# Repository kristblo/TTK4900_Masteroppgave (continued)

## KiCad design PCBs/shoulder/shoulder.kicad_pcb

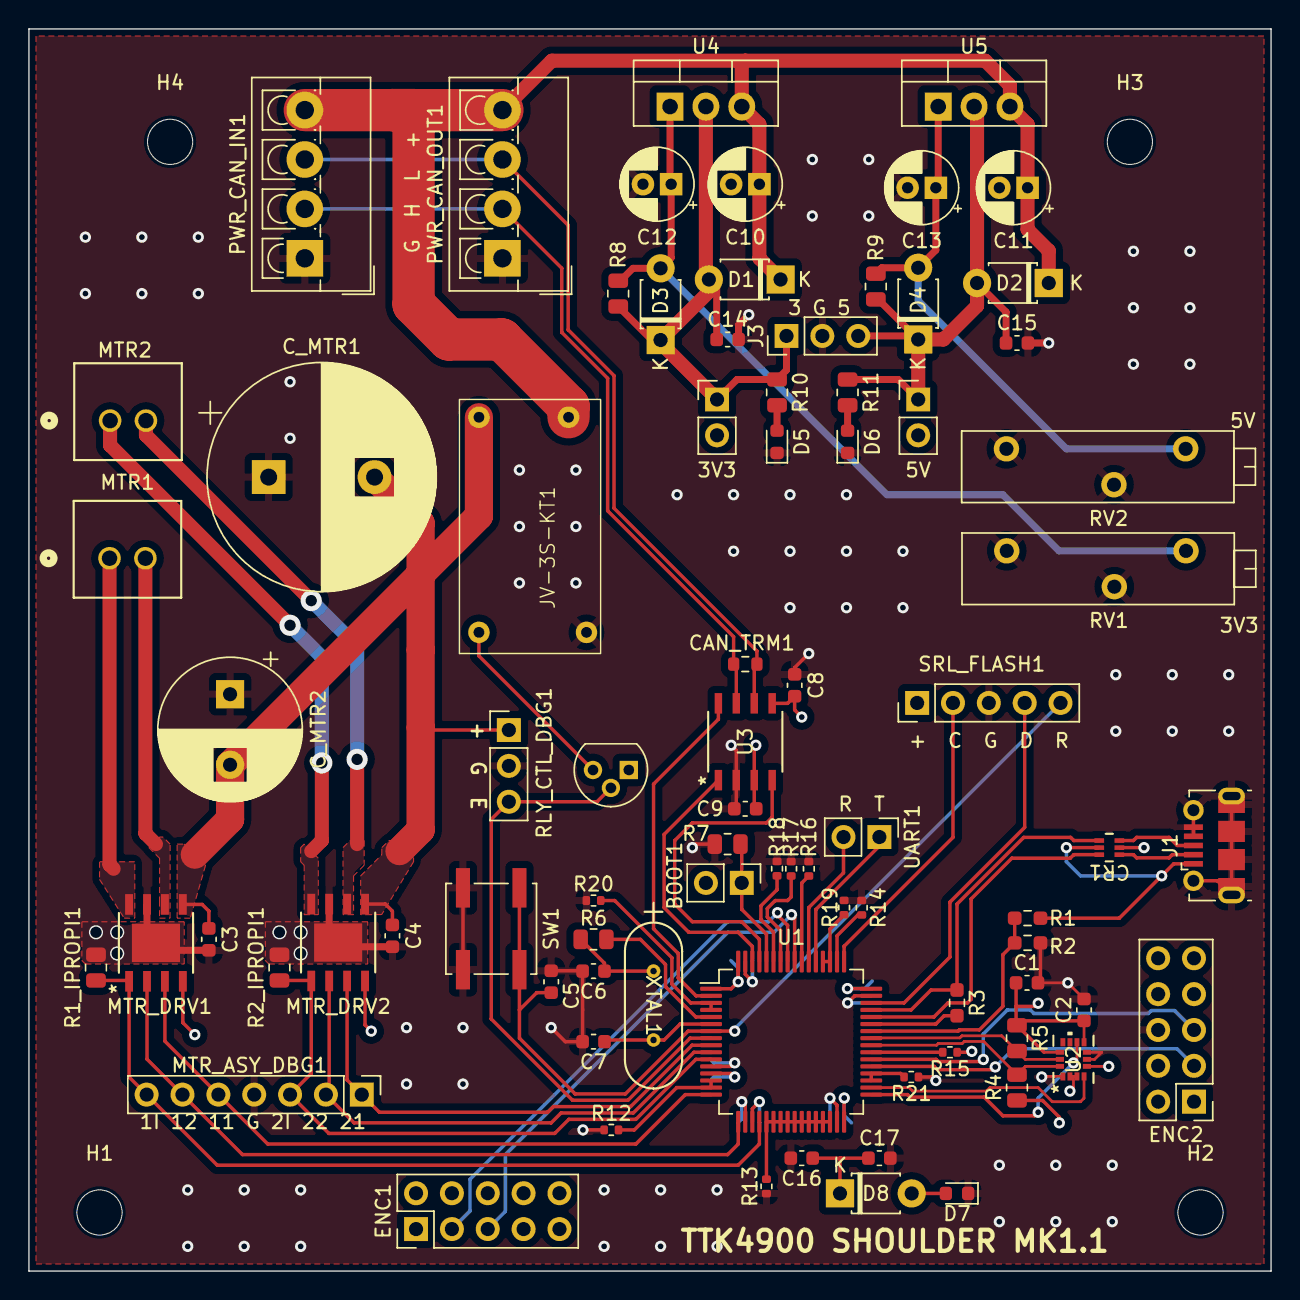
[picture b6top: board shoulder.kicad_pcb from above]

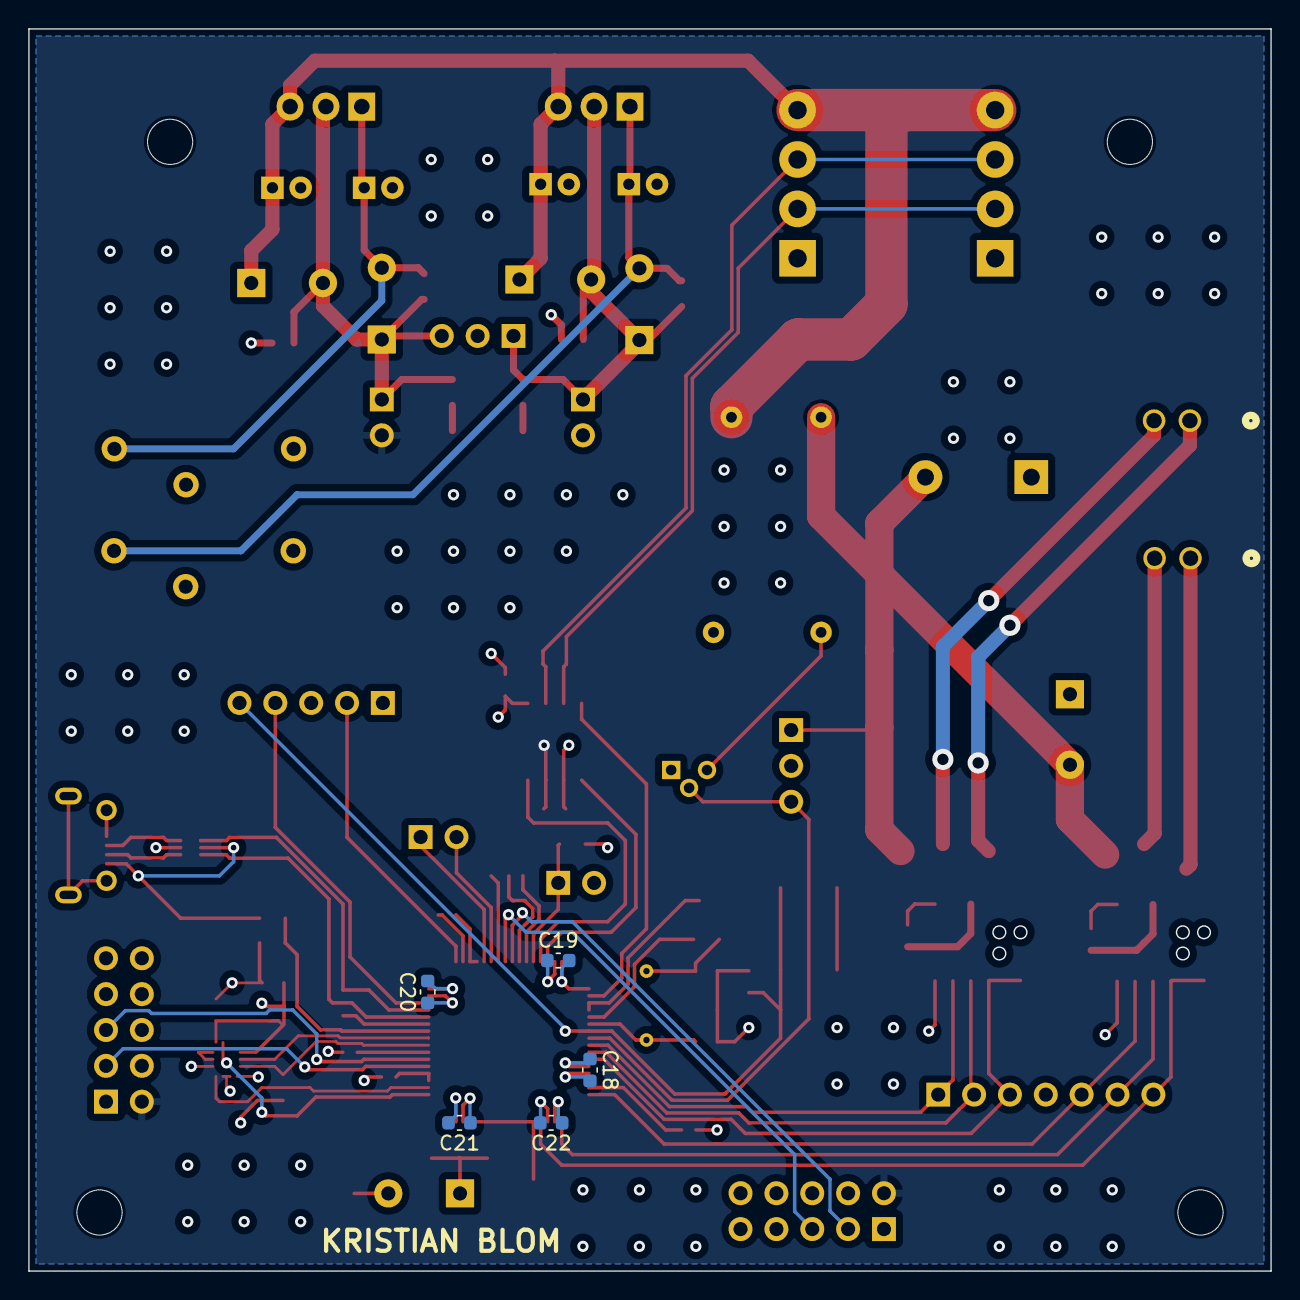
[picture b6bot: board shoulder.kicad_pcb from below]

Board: 4 copper layers, 88.0 x 88.0 mm, 89 parts (5 on the bottom side), 63 nets.

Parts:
BOOT1: BOOTMODE; PinHeader_1x02_P2.54mm_Vertical
C1, C2, C3, C4, C5, C8, C9, C14, C15, C19, C20, C21, C22: 100nF; C_0603_1608Metric
C6, C7: 20pF; C_0603_1608Metric
C10, C11, C12, C13: 10muF; CP_Radial_D5.0mm_P2.00mm
C16: 4.7muF; C_0603_1608Metric
C17: 1muF; C_0603_1608Metric
C18: 10nF; C_0603_1608Metric
CAN_TRM1: 120Ohm; R_0603_1608Metric
CR1: USBLC6-2P6; SOT-666_STM
C_MTR1: 330muF; CP_Radial_D16.0mm_P7.50mm
C_MTR2: 220muF; CP_Radial_D10.0mm_P5.00mm
D1, D2, D3, D4: IN4005; D_T-1_P5.08mm_Horizontal
D5: LED_3V3; LED_0603_1608Metric
D6: LED_5V; LED_0603_1608Metric
D7: LED; LED_0603_1608Metric
D8: D_Zener; D_T-1_P5.08mm_Horizontal
ENC1, ENC2: Conn_02x05_Odd_Even; PinHeader_2x05_P2.54mm_Vertical
H1, H2, H3, H4: MountingHole; MountingHole_3.2mm_M3
J1: USB_B_Micro; USB_Micro-B_Molex-105017-0001
J2: Conn_01x07; PinHeader_1x07_P2.54mm_Vertical
J3: Conn_01x03; PinHeader_1x03_P2.54mm_Vertical
JP1, JP2: Jumper_2_Open; PinHeader_1x02_P2.54mm_Vertical
JV-3S-KT1: RELAY; JV-3S-KT
MTR1, MTR2: 705430001; 70543-0001_MOL
MTR_DRV1, MTR_DRV2: DRV8251ADDAR; SOIC8_DDA_TEX
PWR_CAN_IN1: Conn_01x04; TerminalBlock_4Ucon_1x04_P3.50mm_Vertical
PWR_CAN_OUT1: Conn_01x04; TerminalBlock_4Ucon_1x04_P3.50mm_Vertical
Q1_RLY_CTRL1: Q_NIGBT_CGE; TO-92
R1: 82k; R_0603_1608Metric_Pad0.98x0.95mm_HandSolder
R1_IPROPI1, R2_IPROPI1: 510Ohm; R_0805_2012Metric
R2: 33k; R_0603_1608Metric_Pad0.98x0.95mm_HandSolder
R3: 1k5; R_0603_1608Metric_Pad0.98x0.95mm_HandSolder
R4, R5: 10k; R_0805_2012Metric
R6: 340Ohm; R_0805_2012Metric
R7: 10kOhm; R_0805_2012Metric
R8, R9: 240Ohm; R_0805_2012Metric
R10, R11: 1k5; R_0805_2012Metric
R12, R13, R14, R15, R16, R17, R18, R19, R20, R21: 40kOhm; R_0402_1005Metric
RLY_CTL_DBG1: Conn_01x03; PinHeader_1x03_P2.54mm_Vertical
RV1: 0,386k; Potentiometer_Bourns_3006P_Horizontal
RV2: 0,706k; Potentiometer_Bourns_3006P_Horizontal
SRL_FLASH1: Conn_01x05; PinHeader_1x05_P2.54mm_Vertical
SW1: RESET; SW_Push_1P1T_NO_CK_KSC6xxJ
U1: STM32F303RETx; LQFP-64_10x10mm_P0.5mm
U2: LSM6DSMTR; LGA-14L_2P5X3X0P83_STM
U3: TJA1057GT/3J; SOT96-1_SO8_NXP
U4, U5: LM317_TO-220; TO-220-3_Vertical
UART1: Conn_01x02; PinHeader_1x02_P2.54mm_Vertical
XTAL1: ABL-16.000MHZ-B2; XTAL_ABL-16_ABR

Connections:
+3V3: BOOT1.2 (B), C1.1, C2.1, C8.1, C16.1, C17.1, C18.2, C19.2, C20.2, C21.2, C22.2, D8.1 (K), JP1.2 (B), MTR_DRV1.4 (VREF), MTR_DRV2.4 (VREF), Q1_RLY_CTRL1.1 (C), R4.1, R5.1, SRL_FLASH1.1, U1.1 (VBAT), U1.13 (VDDA), U1.19 (VDD), U1.32 (VDD), U1.48 (VDD), U1.64 (VDD), U2.2 (SDx), U2.3 (SCx), U2.5 (VDDIO), U2.8 (VDD), U2.12 (CS), U3.5 (VIO)
+5V: C9.1, ENC1.2, ENC2.2, JP2.2 (B), U3.3 (VCC)
+48V: C10.1, C11.1, D1.1 (K), D2.1 (K), JV-3S-KT1.3 (NO), PWR_CAN_IN1.4 (48V), PWR_CAN_OUT1.4 (48V), U4.3 (VI), U5.3 (VI)
/BOOT0: BOOT1.1 (A), R7.2, U1.60 (BOOT0)
/CANH: CAN_TRM1.2, PWR_CAN_IN1.2 (CANH), PWR_CAN_OUT1.2 (CANH), U3.7 (CANH)
/CANL: CAN_TRM1.1, PWR_CAN_IN1.3 (CANL), PWR_CAN_OUT1.3 (CANL), U3.6 (CANL)
/CAN_EN: U1.2 (PC13), U3.8 (S)
/CAN_RX: U1.61 (CAN_RX), U3.4 (RXD)
/CAN_TX: U1.62 (CAN_TX), U3.1 (TXD)
/DRV1_IN1: J2.5, MTR_DRV1.3 (IN1), U1.16 (TIM15_CH1)
/DRV1_IN2: J2.6, MTR_DRV1.2 (IN2), U1.17 (TIM15_CH2)
/DRV1_IPROPI: J2.7, MTR_DRV1.1 (IPROPI), R1_IPROPI1.1, U1.20 (ADC2_IN1)
/DRV2_IN1: J2.1, MTR_DRV2.3 (IN1), U1.9 (TIM1_CH2)
/DRV2_IN2: J2.2, MTR_DRV2.2 (IN2), U1.10 (TIM1_CH3)
/DRV2_IPROPI: J2.3, MTR_DRV2.1 (IPROPI), R2_IPROPI1.1, U1.11 (ADC2_IN9)
/ENC1A: ENC1.5, U1.56 (TIM3_CH1)
/ENC1B: ENC1.3, U1.57 (TIM3_CH2)
/ENC2A: ENC2.5, U1.38 (TIM8_CH2)
/ENC2B: ENC2.3, U1.37 (TIM8_CH1)
/FLASH_CLK: SRL_FLASH1.2, U1.49 (SYS_JTCK-SWCLK)
/FLASH_DIO: SRL_FLASH1.4, U1.46 (SYS_JTMS-SWDIO)
/GND_RES1: R13.2, U1.21 (PA5), U1.22 (PA6), U1.23 (PA7), U1.24 (PC4), U1.25 (PC5), U1.26 (PB0), U1.27 (PB1), U1.28 (PB2), U1.29 (PB10), U1.30 (PB11)
/I2C_SCL: R5.2, U1.41 (I2C3_SCL), U2.13 (SCL)
/I2C_SDA: R4.2, U1.40 (I2C3_SDA), U2.14 (SDA)
/IMU_IN2: U1.33 (PB12), U2.9 (INT2)
/IMU_INT1: U1.34 (PB13), U2.4 (INT1)
/OSC_IN: R6.1, U1.5 (RCC_OSC_IN)
/OSC_OUT: C7.1, U1.6 (RCC_OSC_OUT), XTAL1.2
/RELAY_EN: Q1_RLY_CTRL1.2 (G), RLY_CTL_DBG1.3, U1.8 (PC0)
/RESET: C5.2, SRL_FLASH1.5, SW1.3 (K), SW1.4 (A), U1.7 (NRST)
/UART_RX: U1.54 (UART5_RX), UART1.2
/UART_TX: U1.53 (UART5_TX), UART1.1
/USB_DM: CR1.6 (I/O1), U1.44 (USB_DM)
/USB_DP: CR1.4 (I/O2), R3.1, U1.45 (USB_DP)
/USB_DP_DRV: R3.2, U1.43 (PA10)
/USB_VBUS: R1.2, R2.1, U1.42 (PA9)
GND: C1.2, C2.2, C3.1, C4.1, C5.1, C6.2, C7.2, C8.2, C9.2, C10.2, C11.2, C12.2, C13.2, C14.2, C15.2, C16.2, C17.2, C18.1, C19.1, C20.1, C21.1, C22.1, CR1.2 (GND), C_MTR1.1, C_MTR2.1, D5.1 (K), D6.1 (K), D7.1 (K), ENC1.6, ENC2.6, J1.4 (ID), J1.5 (GND), J1.6 (Shield), J2.4, J3.2, JV-3S-KT1.4, MTR_DRV1.7 (GND), MTR_DRV1.9 (EPAD), MTR_DRV2.7 (GND), MTR_DRV2.9 (EPAD), PWR_CAN_IN1.1 (GND), PWR_CAN_OUT1.1 (GND), R1_IPROPI1.2, R2.2, R2_IPROPI1.2, R7.1, R12.1, R13.1, R14.1, R15.1, R16.1, R17.1, R18.1, R19.1, R20.1, R21.1, RLY_CTL_DBG1.2, RV1.1, RV1.2, RV2.1, RV2.2, SRL_FLASH1.3, SW1.1, SW1.2, U1.12 (VSSA), U1.18 (VSS), U1.31 (VSS), U1.47 (VSS), U1.63 (VSS), U2.1 (SDO/SA0), U2.6 (GND), U2.7 (GND), U3.2 (GND)
unnamed: C6.1, R6.2, XTAL1.1
unnamed: CR1.5 (VBUS), J1.1 (VBUS), R1.1
unnamed: C14.1, D1.2 (A), D3.1 (K), J3.1, JP1.1 (A), R8.1, R10.1, U4.2 (VO)
unnamed: C15.1, D2.2 (A), D4.1 (K), J3.3, JP2.1 (A), R9.1, R11.1, U5.2 (VO)
unnamed: C12.1, D3.2 (A), R8.2, RV1.3, U4.1 (ADJ)
unnamed: C13.1, D4.2 (A), R9.2, RV2.3, U5.1 (ADJ)
unnamed: D5.2 (A), R10.2
unnamed: D6.2 (A), R11.2
unnamed: D7.2 (A), D8.2 (A)
unnamed: CR1.3 (I/O2), J1.3 (D+)
unnamed: CR1.1 (I/O1), J1.2 (D-)
unnamed: C3.2, C4.2, C_MTR1.2, C_MTR2.2, JV-3S-KT1.2 (COM), MTR_DRV1.5 (VM), MTR_DRV2.5 (VM), RLY_CTL_DBG1.1
unnamed: MTR1.1 (IN), MTR_DRV1.8 (OUT2)
unnamed: MTR1.2 (OUT), MTR_DRV1.6 (OUT1)
unnamed: MTR2.1 (IN), MTR_DRV2.8 (OUT2)
unnamed: MTR2.2 (OUT), MTR_DRV2.6 (OUT1)
unnamed: JV-3S-KT1.1, Q1_RLY_CTRL1.3 (E)
unnamed: R12.2, U1.14 (PA0), U1.15 (PA1)
unnamed: R14.2, U1.50 (PA15)
unnamed: R16.2, U1.55 (PB3)
unnamed: R17.2, U1.58 (I2C1_SCL)
unnamed: R18.2, U1.59 (I2C1_SDA)
unnamed: R21.2, U1.35 (PB14), U1.36 (PB15)
unnamed: R15.2, U1.39 (PC8)
unnamed: R19.2, U1.51 (PC10), U1.52 (PC11)
unnamed: R20.2, U1.3 (PC14), U1.4 (PC15)

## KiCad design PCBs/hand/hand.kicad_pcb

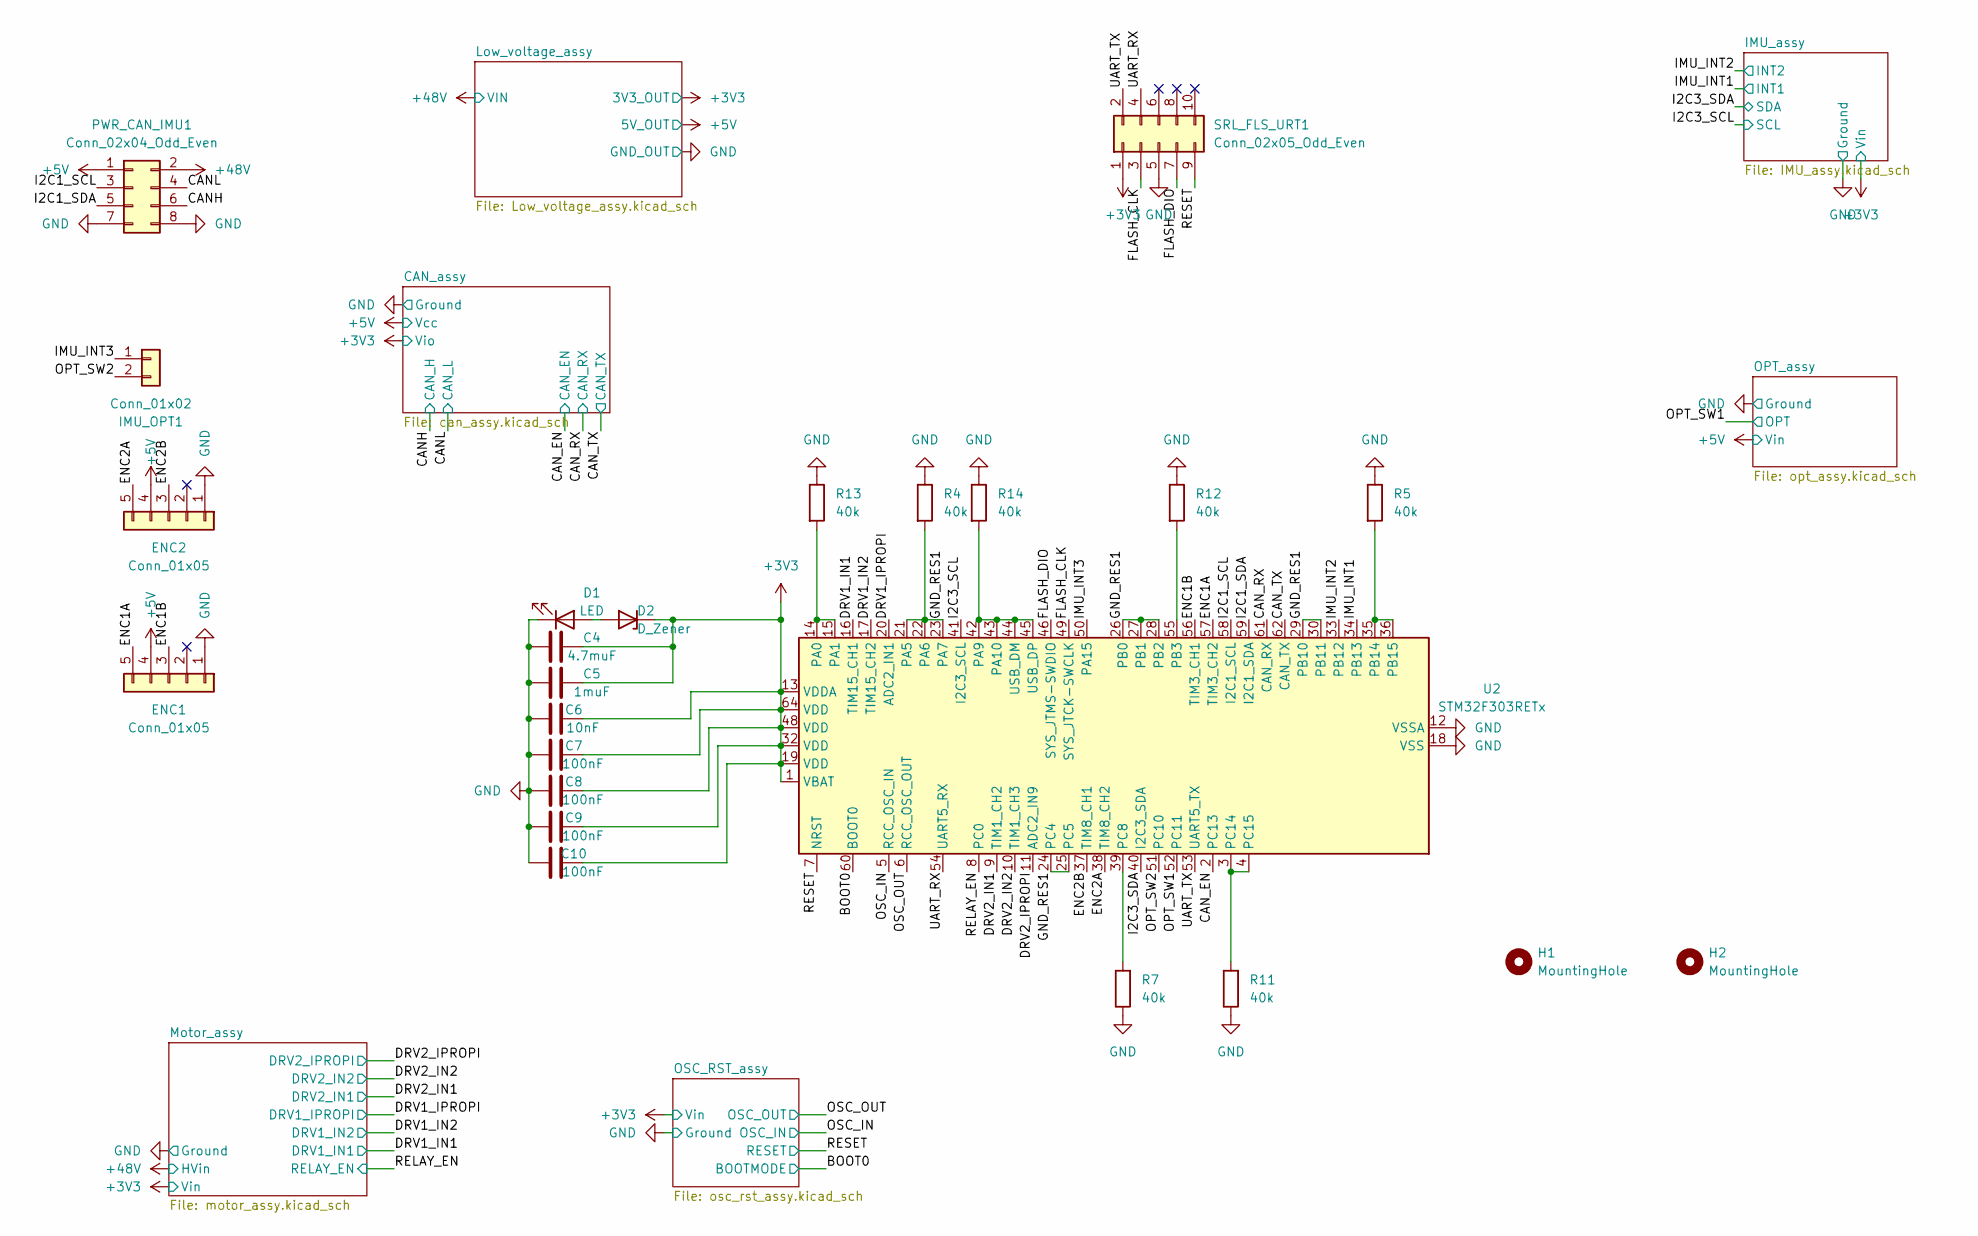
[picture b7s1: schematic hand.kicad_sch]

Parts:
C4: 4.7muF; C_0603_1608Metric
C5: 1muF; C_0603_1608Metric
C6: 10nF; C_0603_1608Metric
C7, C8, C9, C10: 100nF; C_0603_1608Metric
D1: LED; LED_0603_1608Metric
D2: D_Zener; D_T-1_P5.08mm_Horizontal
ENC1, ENC2: Conn_01x05; PinSocket_1x05_P2.54mm_Vertical
H1, H2: MountingHole; MountingHole_2.2mm_M2
IMU_OPT1: Conn_01x02; PinHeader_1x02_P2.54mm_Vertical
PWR_CAN_IMU1: Conn_02x04_Odd_Even; PinHeader_2x04_P2.54mm_Vertical
R4, R5, R7, R11, R12, R13, R14: 40k; R_0402_1005Metric
SRL_FLS_URT1: Conn_02x05_Odd_Even; PinHeader_2x05_P2.54mm_Horizontal
U2: STM32F303RETx; LQFP-64_10x10mm_P0.5mm

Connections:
/BOOT0: U2.60 (BOOT0); also elsewhere on the board
/CANH: PWR_CAN_IMU1.6; also elsewhere on the board
/CANL: PWR_CAN_IMU1.4; also elsewhere on the board
/CAN_EN: U2.2 (PC13); also elsewhere on the board
/CAN_RX: U2.61 (CAN_RX); also elsewhere on the board
/CAN_TX: U2.62 (CAN_TX); also elsewhere on the board
/DRV1_IN1: U2.16 (TIM15_CH1); also elsewhere on the board
/DRV1_IN2: U2.17 (TIM15_CH2); also elsewhere on the board
/DRV1_IPROPI: U2.20 (ADC2_IN1); also elsewhere on the board
/DRV2_IN1: U2.9 (TIM1_CH2); also elsewhere on the board
/DRV2_IN2: U2.10 (TIM1_CH3); also elsewhere on the board
/DRV2_IPROPI: U2.11 (ADC2_IN9); also elsewhere on the board
/ENC1A: ENC1.5, U2.57 (TIM3_CH2)
/ENC1B: ENC1.3, U2.56 (TIM3_CH1)
/ENC2A: ENC2.5, U2.38 (TIM8_CH2)
/ENC2B: ENC2.3, U2.37 (TIM8_CH1)
/FLASH_CLK: SRL_FLS_URT1.3, U2.49 (SYS_JTCK-SWCLK)
/FLASH_DIO: SRL_FLS_URT1.7, U2.46 (SYS_JTMS-SWDIO)
/I2C1_SCL: PWR_CAN_IMU1.3, U2.58 (I2C1_SCL)
/I2C1_SDA: PWR_CAN_IMU1.5, U2.59 (I2C1_SDA)
/I2C3_SCL: U2.41 (I2C3_SCL); also elsewhere on the board
/I2C3_SDA: U2.40 (I2C3_SDA); also elsewhere on the board
/IMU_INT1: U2.34 (PB13); also elsewhere on the board
/IMU_INT2: U2.33 (PB12); also elsewhere on the board
/IMU_INT3: IMU_OPT1.1, U2.50 (PA15)
/OPT_SW1: U2.52 (PC11); also elsewhere on the board
/OPT_SW2: IMU_OPT1.2, U2.51 (PC10)
/OSC_IN: U2.5 (RCC_OSC_IN); also elsewhere on the board
/OSC_OUT: U2.6 (RCC_OSC_OUT); also elsewhere on the board
/RELAY_EN: U2.8 (PC0); also elsewhere on the board
/RESET: SRL_FLS_URT1.9, U2.7 (NRST); also elsewhere on the board
/UART_RX: SRL_FLS_URT1.4, U2.54 (UART5_RX)
/UART_TX: SRL_FLS_URT1.2, U2.53 (UART5_TX)
unnamed: D1.2 (A), D2.2 (A)
unnamed: R13.2, U2.14 (PA0), U2.15 (PA1)
unnamed: R14.2, U2.42 (PA9), U2.43 (PA10), U2.44 (USB_DM), U2.45 (USB_DP)
unnamed: R12.2, U2.55 (PB3)
unnamed: R5.2, U2.35 (PB14), U2.36 (PB15)
unnamed: R7.2, U2.39 (PC8)
unnamed: R11.2, U2.3 (PC14), U2.4 (PC15)

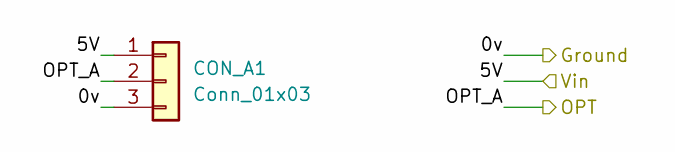
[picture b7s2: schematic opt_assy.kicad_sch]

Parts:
CON_A1: Conn_01x03; PinHeader_1x03_P2.54mm_Vertical

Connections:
/OPT_SW1: CON_A1.2; also elsewhere on the board

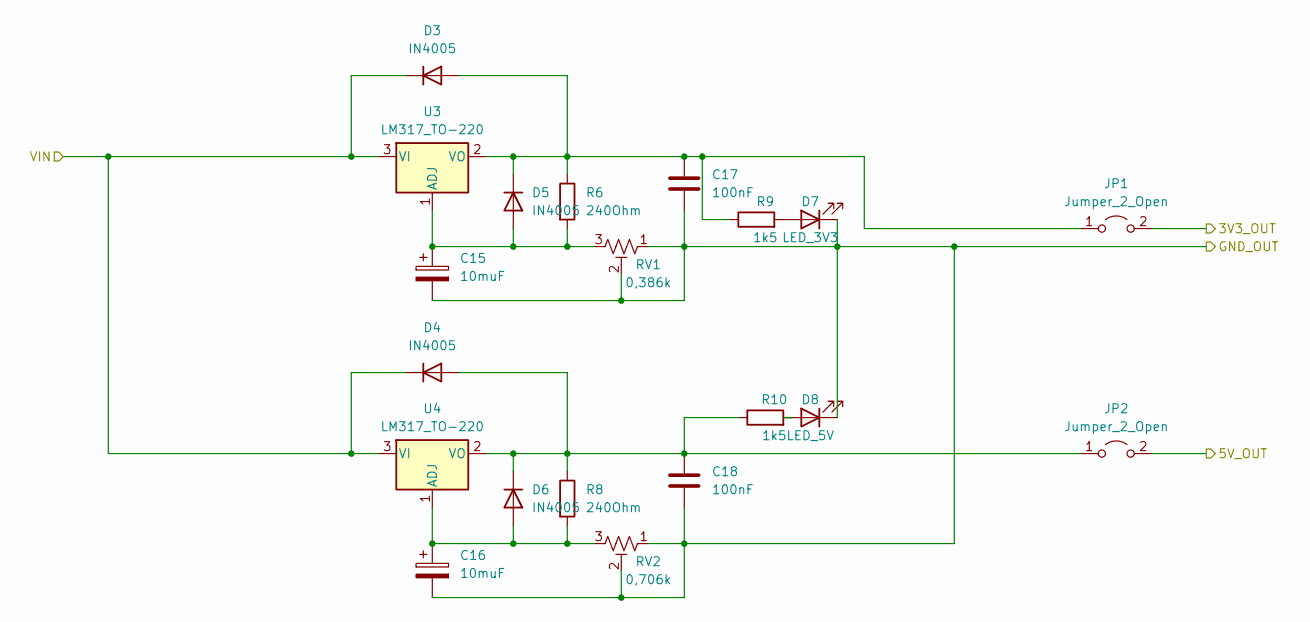
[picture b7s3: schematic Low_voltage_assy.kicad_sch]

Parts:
C15, C16: 10muF; CP_Axial_L10.0mm_D4.5mm_P15.00mm_Horizontal
C17, C18: 100nF; C_0603_1608Metric
D3, D4, D5, D6: IN4005; D_T-1_P5.08mm_Horizontal
D7: LED_3V3; LED_0603_1608Metric
D8: LED_5V; LED_0603_1608Metric
JP1, JP2: Jumper_2_Open; PinHeader_1x02_P2.54mm_Horizontal
R6, R8: 240Ohm; R_0805_2012Metric
R9, R10: 1k5; R_0805_2012Metric
RV1: 0,386k; Potentiometer_Bourns_3006P_Horizontal
RV2: 0,706k; Potentiometer_Bourns_3006P_Horizontal
U3, U4: LM317_TO-220; TO-220-3_Horizontal_TabDown

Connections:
unnamed: C17.1, D3.2 (A), D5.1 (K), JP1.1 (A), R6.1, R9.1, U3.2 (VO)
unnamed: C18.1, D4.2 (A), D6.1 (K), JP2.1 (A), R8.1, R10.1, U4.2 (VO)
unnamed: C15.1, D5.2 (A), R6.2, RV1.3, U3.1 (ADJ)
unnamed: C16.1, D6.2 (A), R8.2, RV2.3, U4.1 (ADJ)
unnamed: D7.2 (A), R9.2
unnamed: D8.2 (A), R10.2

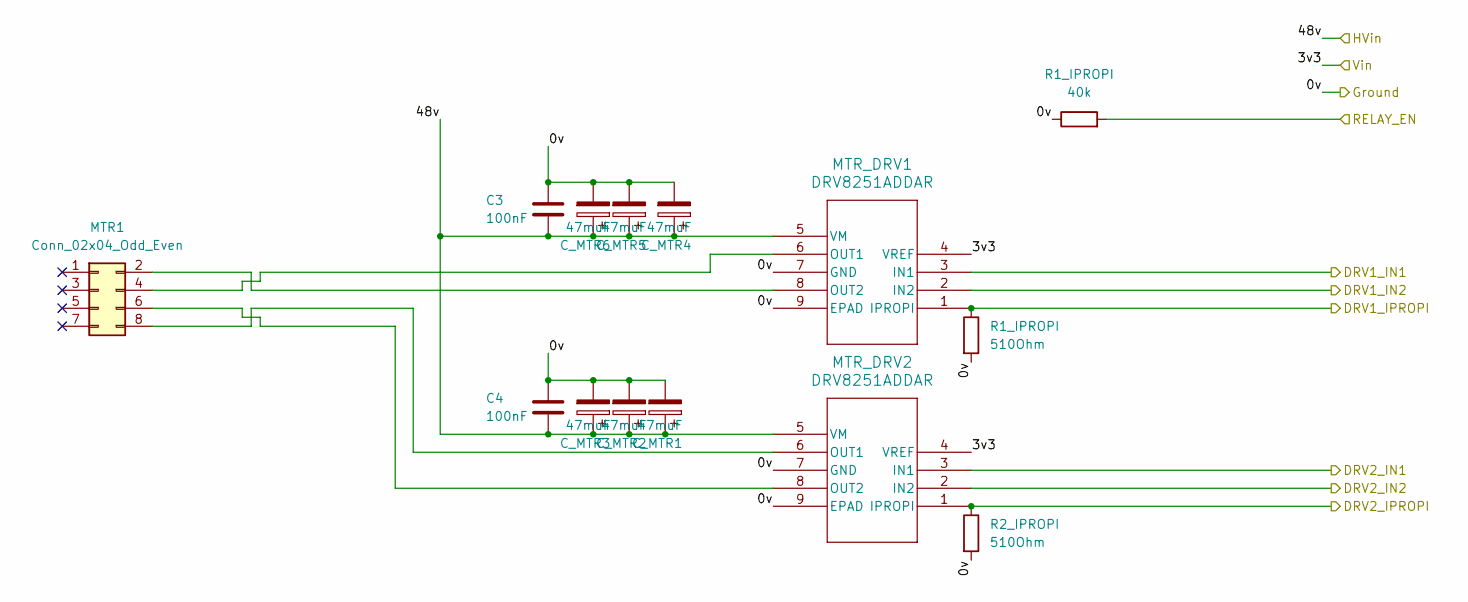
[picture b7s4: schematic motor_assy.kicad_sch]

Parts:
C3, C4: 100nF; C_0603_1608Metric
C_MTR1, C_MTR2, C_MTR3, C_MTR4, C_MTR5, C_MTR6: 47muF; CP_Elec_6.3x7.7
MTR1: Conn_02x04_Odd_Even; PinHeader_2x04_P2.54mm_Vertical
MTR_DRV1, MTR_DRV2: DRV8251ADDAR; SOIC8_DDA_TEX
R1_IPROPI: 40k; R_0402_1005Metric
R2_IPROPI: 510Ohm; R_0805_2012Metric

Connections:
/DRV1_IN1: MTR_DRV1.3 (IN1); also elsewhere on the board
/DRV1_IN2: MTR_DRV1.2 (IN2); also elsewhere on the board
/DRV1_IPROPI: MTR_DRV1.1 (IPROPI); also elsewhere on the board
/DRV2_IN1: MTR_DRV2.3 (IN1); also elsewhere on the board
/DRV2_IN2: MTR_DRV2.2 (IN2); also elsewhere on the board
/DRV2_IPROPI: MTR_DRV2.1 (IPROPI); also elsewhere on the board
unnamed: MTR1.2, MTR_DRV1.8 (OUT2)
unnamed: MTR1.4, MTR_DRV1.6 (OUT1)
unnamed: MTR1.6, MTR_DRV2.8 (OUT2)
unnamed: MTR1.8, MTR_DRV2.6 (OUT1)

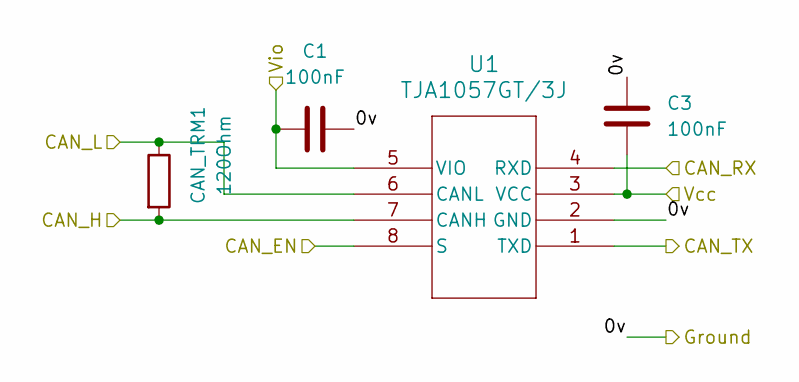
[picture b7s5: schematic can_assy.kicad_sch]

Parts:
C1, C3: 100nF; C_0603_1608Metric
CAN_TRM1: 120Ohm; R_0603_1608Metric
U1: TJA1057GT/3J; SOT96-1_SO8_NXP

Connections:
/CANH: CAN_TRM1.2, U1.7 (CANH); also elsewhere on the board
/CANL: CAN_TRM1.1, U1.6 (CANL); also elsewhere on the board
/CAN_EN: U1.8 (S); also elsewhere on the board
/CAN_RX: U1.4 (RXD); also elsewhere on the board
/CAN_TX: U1.1 (TXD); also elsewhere on the board

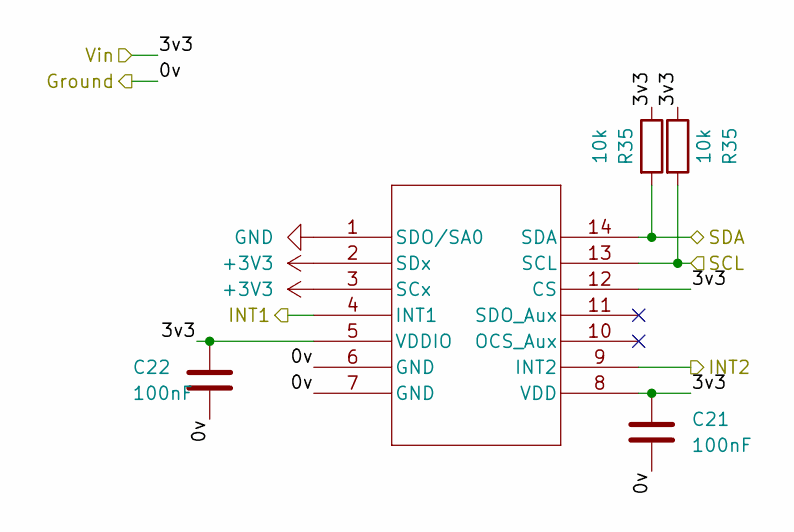
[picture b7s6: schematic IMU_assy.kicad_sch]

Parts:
C21, C22: 100nF; C_0402_1005Metric
R35: 10k; R_0402_1005Metric
U5: LSM6DSMTR; LGA-14L_2P5X3X0P83_STM

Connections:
/I2C3_SCL: U5.13 (SCL); also elsewhere on the board
/I2C3_SDA: U5.14 (SDA); also elsewhere on the board
/IMU_INT1: U5.4 (INT1); also elsewhere on the board
/IMU_INT2: U5.9 (INT2); also elsewhere on the board

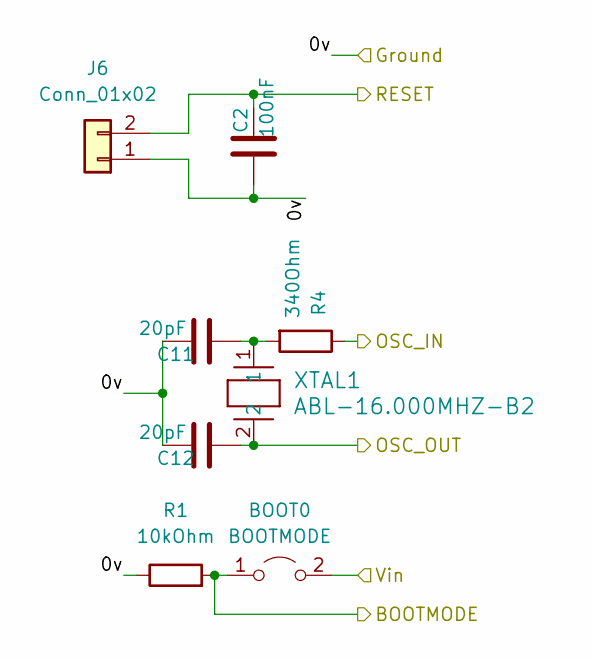
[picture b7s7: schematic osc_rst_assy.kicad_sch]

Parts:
BOOT0: BOOTMODE; PinHeader_1x02_P2.54mm_Horizontal
C2: 100nF; C_0603_1608Metric
C11, C12: 20pF; C_0603_1608Metric
J6: Conn_01x02; PinHeader_1x02_P2.54mm_Horizontal
R1: 10kOhm; R_0805_2012Metric
R4: 340Ohm; R_0805_2012Metric
XTAL1: ABL-16.000MHZ-B2; XTAL_ABL-16_ABR

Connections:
/BOOT0: R1.2; also elsewhere on the board
/OSC_OUT: C12.1, XTAL1.2; also elsewhere on the board
/RESET: J6.2; also elsewhere on the board

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
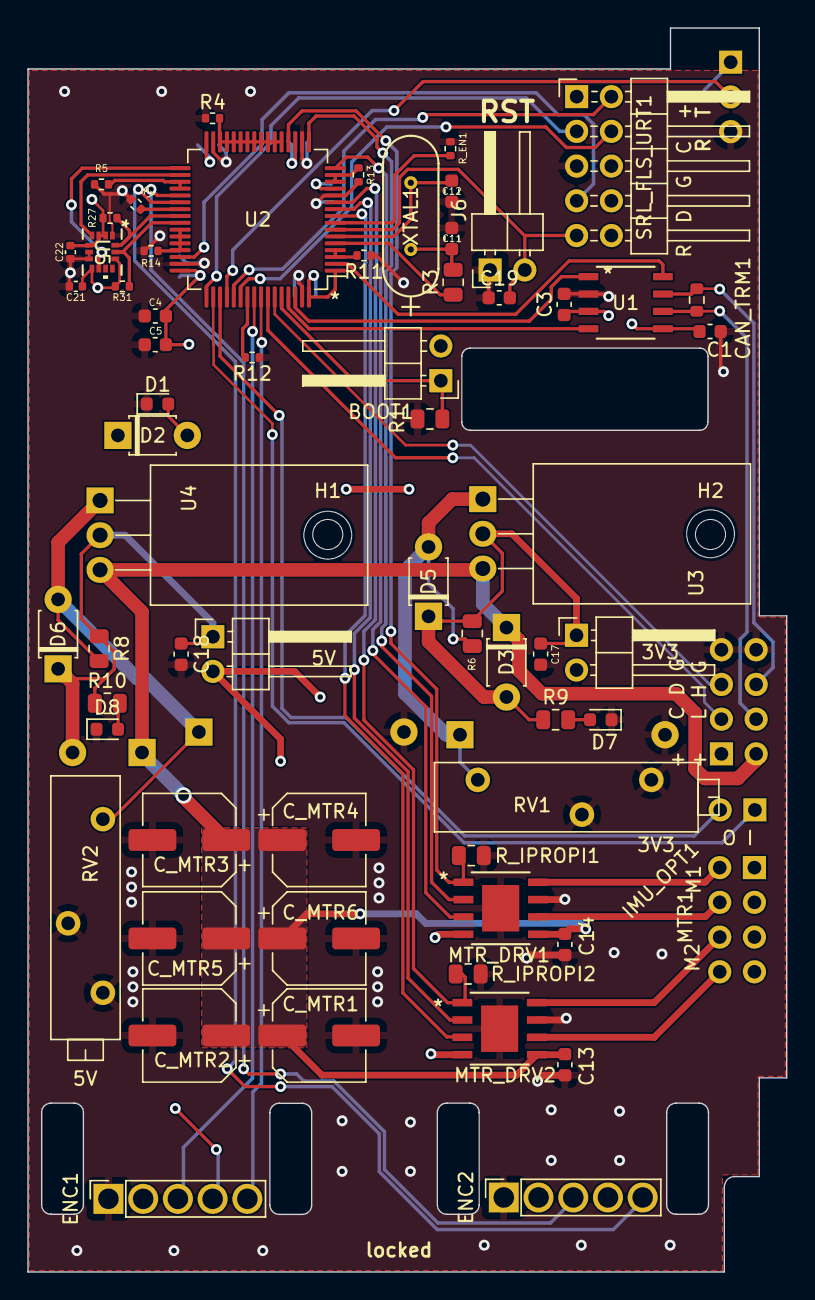
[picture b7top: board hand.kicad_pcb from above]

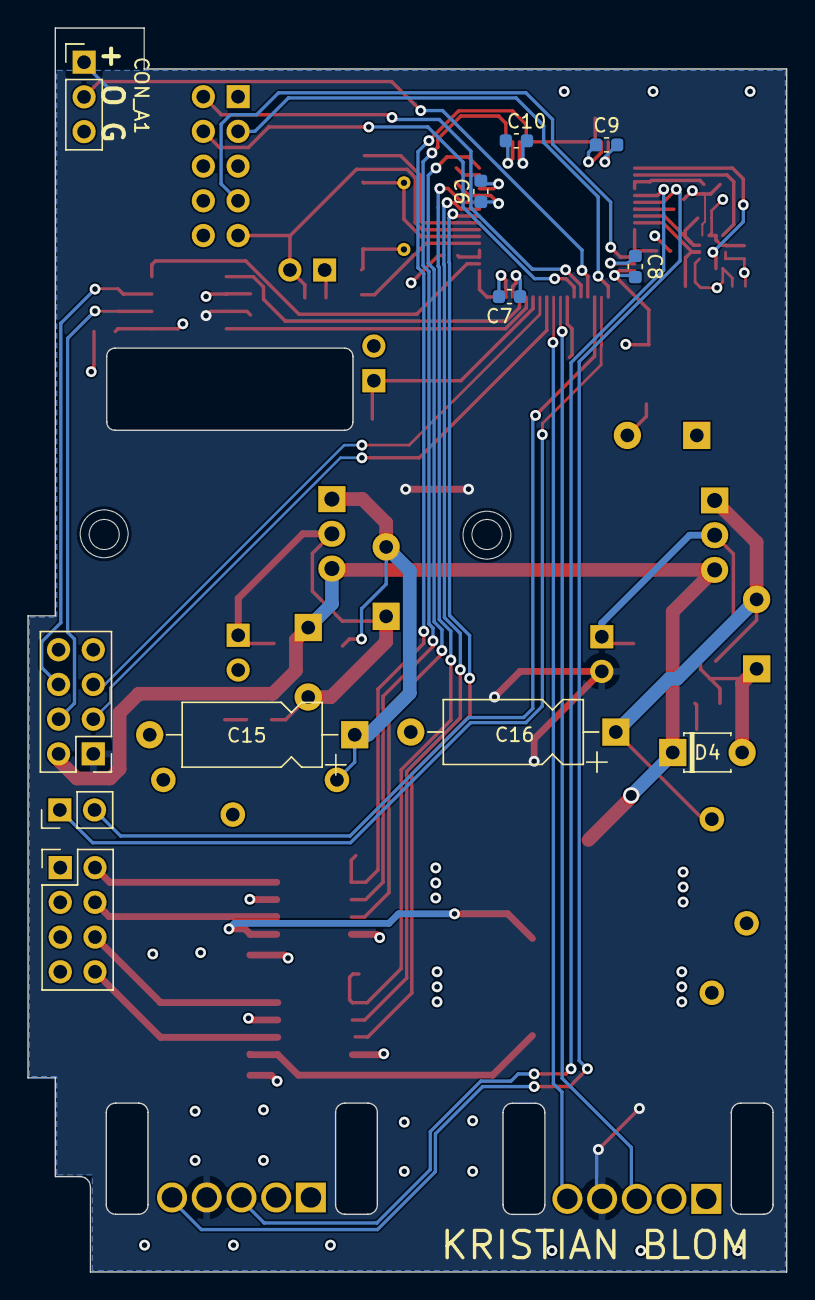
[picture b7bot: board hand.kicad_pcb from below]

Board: 4 copper layers, 55.5 x 91.0 mm, 76 parts (12 on the bottom side), 56 nets.

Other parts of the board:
BOOT1: BOOTMODE; PinHeader_1x02_P2.54mm_Horizontal
C13, C14, C19: 100nF; C_0603_1608Metric
R3: 340Ohm; R_0805_2012Metric
R27, R31: 10k; R_0402_1005Metric
R_EN1: 40k; R_0402_1005Metric
R_IPROPI1, R_IPROPI2: 510Ohm; R_0805_2012Metric

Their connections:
/BOOT0: BOOT1.1 (A); also elsewhere on the board
/DRV1_IPROPI: R_IPROPI1.1; also elsewhere on the board
/DRV2_IPROPI: R_IPROPI2.1; also elsewhere on the board
/I2C3_SCL: R31.2; also elsewhere on the board
/I2C3_SDA: R27.2; also elsewhere on the board
/OSC_IN: R3.1; also elsewhere on the board
/RELAY_EN: R_EN1.2; also elsewhere on the board
/RESET: C19.2; also elsewhere on the board

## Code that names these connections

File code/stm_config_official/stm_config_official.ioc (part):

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Mcu.Name=STM32F303R(D-E)Tx
Mcu.Package=LQFP64
Mcu.UserName=STM32F303RETx
PA10.GPIOParameters=GPIO_Label
PA10.GPIO_Label=USB_DP_DRV
PA10.Signal=GPIO_Output
PA11.Mode=Device
PA11.Signal=USB_DM
PA12.Mode=Device
PA12.Signal=USB_DP
PA13.Mode=Serial_Wire
PA13.Signal=SYS_JTMS-SWDIO
PA14.Mode=Serial_Wire
PA14.Signal=SYS_JTCK-SWCLK
PA15.GPIOParameters=GPIO_Label
PA15.GPIO_Label=END_SW_BAK
PA15.Signal=GPXTI15
PA2.GPIOParameters=GPIO_Label
PA2.GPIO_Label=DRV1_IN1
PA2.Signal=S_TIM15_CH1
PA3.GPIOParameters=GPIO_Label
PA3.GPIO_Label=DRV1_IN2
PA3.Signal=S_TIM15_CH2
PA4.GPIOParameters=GPIO_Label
PA4.GPIO_Label=DRV1_VIP
PA4.Mode=IN1-Single-Ended
PA4.Signal=ADC2_IN1
PA5.GPIOParameters=GPIO_Label,GPIO_ModeDefaultEXTI
PA5.GPIO_Label=END_SW
PA5.GPIO_ModeDefaultEXTI=GPIO_MODE_IT_RISING
PA5.Signal=GPXTI5
PA8.Mode=I2C
PA8.Signal=I2C3_SCL
PA9.GPIOParameters=GPIO_Label
PA9.GPIO_Label=USB_VB
PA9.Signal=GPXTI9
PB12.GPIOParameters=GPIO_Label
PB12.GPIO_Label=IMU_INT2
PB12.Signal=GPIO_Output
PB13.GPIOParameters=GPIO_Label
PB13.GPIO_Label=IMU_INT1
PB13.Signal=GPIO_Output
PB4.GPIOParameters=GPIO_Label
PB4.GPIO_Label=ENC1A
PB4.Signal=S_TIM3_CH1
PB5.GPIOParameters=GPIO_Label
PB5.GPIO_Label=ENC1B
PB5.Signal=S_TIM3_CH2
PB6.Mode=I2C
PB6.Signal=I2C1_SCL
PB7.Mode=I2C
PB7.Signal=I2C1_SDA
PB8.Mode=CAN_Activate
PB8.Signal=CAN_RX
PB9.Mode=CAN_Activate
PB9.Signal=CAN_TX
PC0.GPIOParameters=GPIO_Label
PC0.GPIO_Label=RELAY_EN
PC0.Signal=GPIO_Output
PC1.GPIOParameters=GPIO_Label
PC1.GPIO_Label=DRV2_IN1
PC1.Signal=S_TIM1_CH2
PC10.GPIOParameters=GPIO_Label
PC10.GPIO_Label=OPT_SW2
PC10.Signal=GPXTI10
PC11.GPIOParameters=GPIO_Label,GPIO_ModeDefaultEXTI
PC11.GPIO_Label=OPT_SW1
PC11.GPIO_ModeDefaultEXTI=GPIO_MODE_IT_FALLING
PC11.Signal=GPXTI11
PC12.Mode=Asynchronous
PC12.Signal=UART5_TX
PC13.GPIOParameters=GPIO_Label
PC13.GPIO_Label=CAN_EN
PC13.Signal=GPIO_Output
PC2.GPIOParameters=GPIO_Label
PC2.GPIO_Label=DRV2_IN2
PC2.Signal=S_TIM1_CH3
PC3.GPIOParameters=GPIO_Label
PC3.GPIO_Label=DRV2_VIP
PC3.Signal=ADCx_IN9
PC6.GPIOParameters=GPIO_Label
PC6.GPIO_Label=ENC2B
PC6.Signal=S_TIM8_CH1
PC7.GPIOParameters=GPIO_Label
PC7.GPIO_Label=ENC2A
PC7.Signal=S_TIM8_CH2
PC9.Mode=I2C
PC9.Signal=I2C3_SDA
PD2.Mode=Asynchronous
PD2.Signal=UART5_RX
PF0-OSC_IN.Mode=HSE-External-Oscillator
PF0-OSC_IN.Signal=RCC_OSC_IN
PF1-OSC_OUT.Mode=HSE-External-Oscillator
PF1-OSC_OUT.Signal=RCC_OSC_OUT
RCC.HSE_VALUE=16000000
RCC.SYSCLKFreq_VALUE=72000000
RCC.SYSCLKSourceVirtual=RCC_SYSCLKSOURCE_PLLCLK
board=custom

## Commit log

2024-01-17 Added ignr, folderer structure, some documentation
2024-01-17 Shoulder motor assy almost done. Need to find a library for the 2N551 NPN and redo the circuit. Ensure that the footprint pinout is correct
2024-01-18 Shoulder done, see today's journal notes. Starting torso
2024-01-18 Torso schematic almost complete, missing pulldowns and a decision on the I2C header matter
2024-01-19 Torso all but complete, making bogie before checking the last mark
2024-01-19 Torso, bogie and rail complete. Next up: revise hand and IMU board in conjunction
2024-01-24 Hand schematic changes complete. Found IMU dc buck, see journal. Next up: trace hand
2024-01-25 Updated ign with ever more variations of autosaves. Finished tracing hand, probably need new footprint for encoders. Next up: find footprints, redo IMU board
2024-01-26 All revisions finished, MK1.1 ready for gerber generation
2024-01-26 Separated Hand B as separate Kicad project. Next up: gerber generation
2024-01-26 All gerbers generated. Next up: BOM
2024-01-26 Created BOM, ordered all PCBs
2024-01-26 All non-OV components ordered. Next up: Get OV components, ready arm for HW installation
2024-02-07 Nothing particular, preparing for assembly
2024-02-16 Journal, ready for brnch to testing
2024-02-23 UART good, no contact with IMU board or hand IMU. Getting Adafruit unit instead. Next up: motor drivers
2024-02-23 Shoulder Z axis broken, X axis operational. Next up: motor drivers
2024-02-23 Motor drivers complete. Next up: CAN. Also, put a heat sink on the shoulder sooner rather than later
2024-02-24 CAN loopback mode operational on torso. Next up: normal mode
2024-02-24 CAN working. Next up: arm integration!
2024-03-09 Updated ign
2024-03-09 Working UART input for basic control. All motors work. Next up: switch interrupts
2024-03-10 Preparing for brnch change
2024-03-10 tests
2024-03-10 Working loopback tested on shoulder
2024-03-10 Communication between hand and torso OK. Used ID 10A for torso, 10B for hand
2024-03-10 Tried CAN again, did not work
2024-03-10 CAN working with rx and tx in function wrappers
2024-03-10 Still can't get CAN to work on this branch. Works on the other one though, so next up is to start building the final architecture on the main branch around the CAN infrastructure
2024-03-10 Added gofwd on twist upon receiving the CAN msg, so that is indeed possible to do.
2024-03-12 Merged stm config, journal and ext doc from hw_verification
2024-03-12 began CAN implementation
2024-03-12 various
2024-03-12 Working on getting this closer to the format in main
2024-03-12 Got rx working by fetching can.c from the can_verification branch. No idea what the difference was, which no doubt will bite me later
2024-03-12 CAN is working again. Committing to find out if code generation breaks it
2024-03-12 Got the CAN backbone structure up and running. Need to read more about interrupts, and look at Byggern
2024-03-15 string parsing and motor control works, committing as a savepoint
2024-03-16 String commands and motor control works, tested on torso. Next up: Implement structs for other motors
2024-03-16 local control functional on all motors. Next up: CAN
2024-03-17 CAN control working. Next up: refactoring, prettyfying
2024-03-17 CAN code prettyfied a bit
2024-03-17 Notes before making ready for accelerometer integration
2024-03-22 Committing for safe state. Next up: fix accelerometer can messages
2024-03-23 safe state for CAN. Next up: one last attempt at acc readings
2024-03-23 safe state, accelerometer over CAN appears to work. Next up: move CAN cmd handlers to a separate file.
2024-03-23 moved CAN handler sto separate functions, but not separate files due to cyclical include problem
2024-03-23 reimplemented joint control for all joints, works! Next up: calibrate 0 for shoulder using acc
2024-03-23 Added a new struct for handling incoming accelerometer data, with getters and setters
2024-03-24 Got accelerometer data back, new CAN messaging system seems to work well.
2024-03-25 Starting ADC driver config. Still need to incorporate acc into control loop
2024-03-25 ADC with watchdog interrupt working. Next up: integrate acc, clean up and comment
2024-03-26 Accelerometer integrated into shoulder, committing before comments
2024-03-26 Added more doc, stuck on joint controller
2024-03-30 Documentation complete. Next up: PID and calibration
2024-03-31 Refactored motor driver to use list of motors
2024-03-31 PID complete. Next: calibration
2024-03-31 started on home calibration
2024-04-01 calibration works for individual joints. Next up: all 6 together
2024-04-03 Calibration complete
2024-04-04 so much for cleanup, but the control loop is less spastic. Next up: cleanup
2024-04-09 PIDs are tuned acceptably well, calibration works ish. Preparing for ROS
2024-04-13 Added ROS nodes, urdf, got started on a UART parser for ROS
2024-04-13 got ros integration, shoulder and rail smooth. Next up: add CAN msgs to transfer joint setpoints
2024-04-16 All joints except pinch controllable. Committing before running setup assistant
2024-04-17 various ROS improvements. Next up: PID tuning at varying voltages
2024-04-18 Commiting before merge
2024-04-18 Committing before merge
2024-04-18 pids are tuned, overall works better. Possibly reconsider elbow int action
2024-04-19 added sigmoid function to integral, retuned. Officially done with implementation
2024-04-25 Added simple telemetry. Shoulder calib does not properly work, and shoulder keeps spazzing when perturbed
2024-05-01 added diagrams
2024-05-01 minor code changes after testing at OV. IMPORTANT: IMU deactivated, shoulder limit to 1.5
2024-05-02 Added various diagrams, discovered that I did not merge the PCB folders with after the 1.1 updates
2024-05-02 merged pcbs from improvement phase
2024-05-07 fernet gif and torso fcu
2024-05-07 Added pcb pdfs
2024-05-20 Minor changes to documentation, added diagrams
2024-05-20 Found a minor bug in the voltage cap check, always used motor2 as reference. Likely no harm done. Added diagrams
2024-05-22 Added diagrams, some TODOs in code
2024-05-24 added diagrams, some comments
2024-05-24 Added log files from main loop tests
2024-05-25 Changed CAN handler motorSp to jointSp
2024-05-27 added diagrams, modified logfiles to prettify
2024-05-29 added a bunch of figures, found a crucial error in pid calculation. The sigmoid also squares kpti. fml
2024-05-30 Added include graph
2024-05-31 updated doxy, added doxy build zips
2024-06-08 Added a whole bunch of docs in addition to doing the timer test. Ready for selective mrg w main
2024-06-08 merged changes from timertests, mostly documentation and such. Did not add tim6 config
2024-06-08 finalised before censure curation
2024-06-08 minor change to readme
2024-06-08 unnecessary files deleted
2024-09-26 minimal changes necessary to open for editing in setup assistant while also building and operating as normal
2024-09-26 added cleanup script
2024-09-26 added build script
2024-09-26 got the pincer working by setting the joint type to non-gripper
2024-09-27 Updated control message and control listener nodes to receive pincer value. Halved, as moveit treats the gripper teeth as two joints.
2024-10-01 Got the task planning demo to work. Execute task server connection failure error thingy solved by adding executeTaskSolutionCapability and move group node to pick and place launch demo python script
2024-10-08 got the pnp tutorial working with ORCA. Inconsistent IK solutions, and whether the cylinder loads or not is apparently random, but the code 'works'
2024-10-08 had to rebuild moveit after (due to?) ubuntu updates. Pnp operational w return to calibrated pose
2024-10-19 Rotating bottle and putting it back works. Next up: rotate around arbitrary point
2024-10-20 Rotation around bottle top and insertion of multiple objects works. Next up: rewrite new package from scratch
2024-10-25 barely working demo of tasks. Cannot get the damn thing to stand still. Probably need to figure out passing object info between tasks
2025-08-01 Important: fixed pinch problem by changing the UART message stack, must be mrgd into main. Less important: various tests of task constructions, mostly jank. Committing now in prep for partial mrg wit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
2025-08-07 selective mrg from task brnch, updates rviz config and comms layer to support pinch
2025-08-21 upd buildscript to include all packages
